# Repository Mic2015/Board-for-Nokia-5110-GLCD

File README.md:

# KiCad Board-for-Nokia-5110/3310-GLCD
Breakout board for Nokia 5110/3310 GLCD "clip-in"  support pour Nokia 5110/3310 GLCD à enclipser
All files to create breakout board schematic and PCB and 3D components from KiCad 5.0 and Wings 3D (for the 3D components)
Nokia mod are from :https://github.com/sgreg/kicad-libs/tree/master/footprints/Nokia_5110-3310_LCD.pretty

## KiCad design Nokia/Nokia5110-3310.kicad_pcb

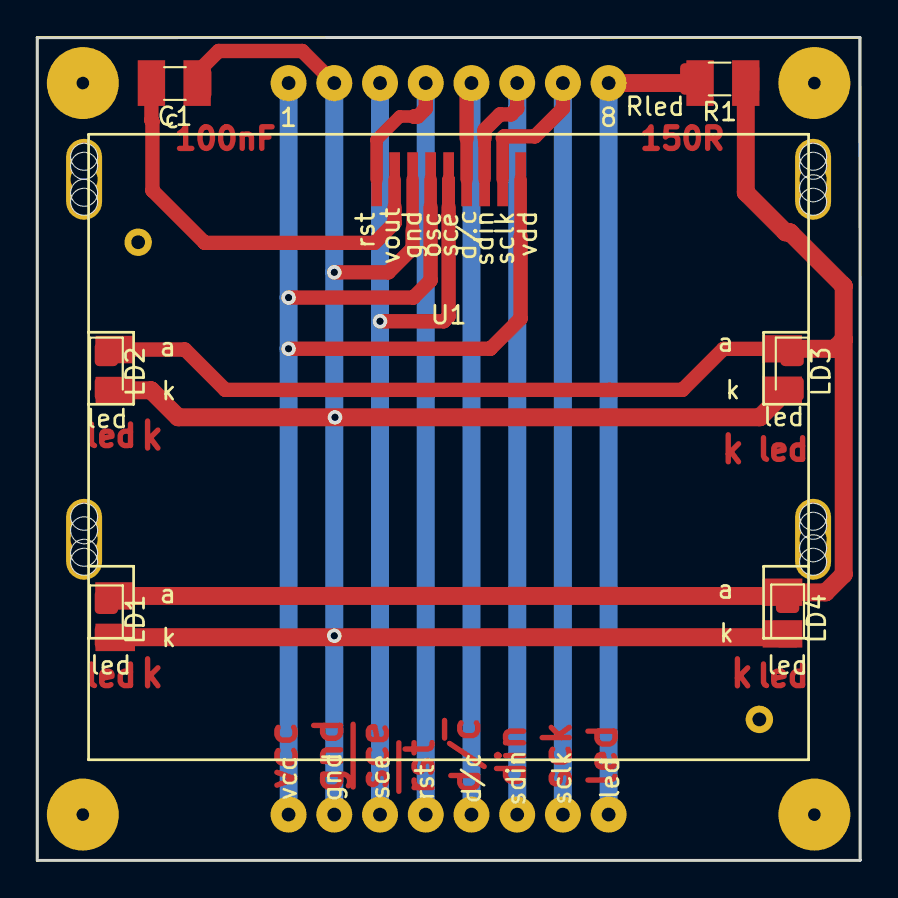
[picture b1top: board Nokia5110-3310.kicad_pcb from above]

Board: 2 copper layers, 45.7 x 45.7 mm, 7 parts (0 on the bottom side), 10 nets.

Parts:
C1: 100nF; C_1206_3216Metric
LD1, LD2, LD3, LD4: LED; LED_0805_2012Metric_Castellated
R1: 150R; R_1206_3216Metric_Pad1.42x1.75mm_HandSolder
U1: Nokia_5110_LCD_BRD_1; Nokia_5110-LCDboard

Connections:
DIN: U1.7, U1.36, U1.46
D~C: U1.6, U1.35, U1.45
GND: C1.1, LD1.2, LD2.2, LD3.2, LD4.2, U1.3, U1.12, U1.16, U1.18, U1.20, U1.22, U1.32, U1.42
LED: R1.2, U1.13, U1.38, U1.48
unnamed: LD1.1, LD2.1, LD3.1, LD4.1, R1.1, U1.14, U1.15, U1.17, U1.19, U1.21
SCK: U1.8, U1.37, U1.47
VCC: U1.4, U1.9, U1.31, U1.41
VOUT: C1.2, U1.2, U1.11
~RST: U1.1, U1.34, U1.44
~SCE: U1.5, U1.33, U1.43
